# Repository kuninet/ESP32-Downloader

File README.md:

# ESP32/ESP8266 Downloader基板

## 概要
* ESP32/ESP8266 Downloader基板です。
* ピン配置は ESP32 Downloader kitに合わせています。
* MOS FET x2個で自動書き込み回路を装備してしています。
* USBシリアルICはCH340Kを使用しています。

## 回路図
[回路図](image/ESP32-Downloder.pdf)

## イメージ

## 参考
* ESP32 Downloader kit
  * https://docs.m5stack.com/ja/accessory/esp32_downloader_kit

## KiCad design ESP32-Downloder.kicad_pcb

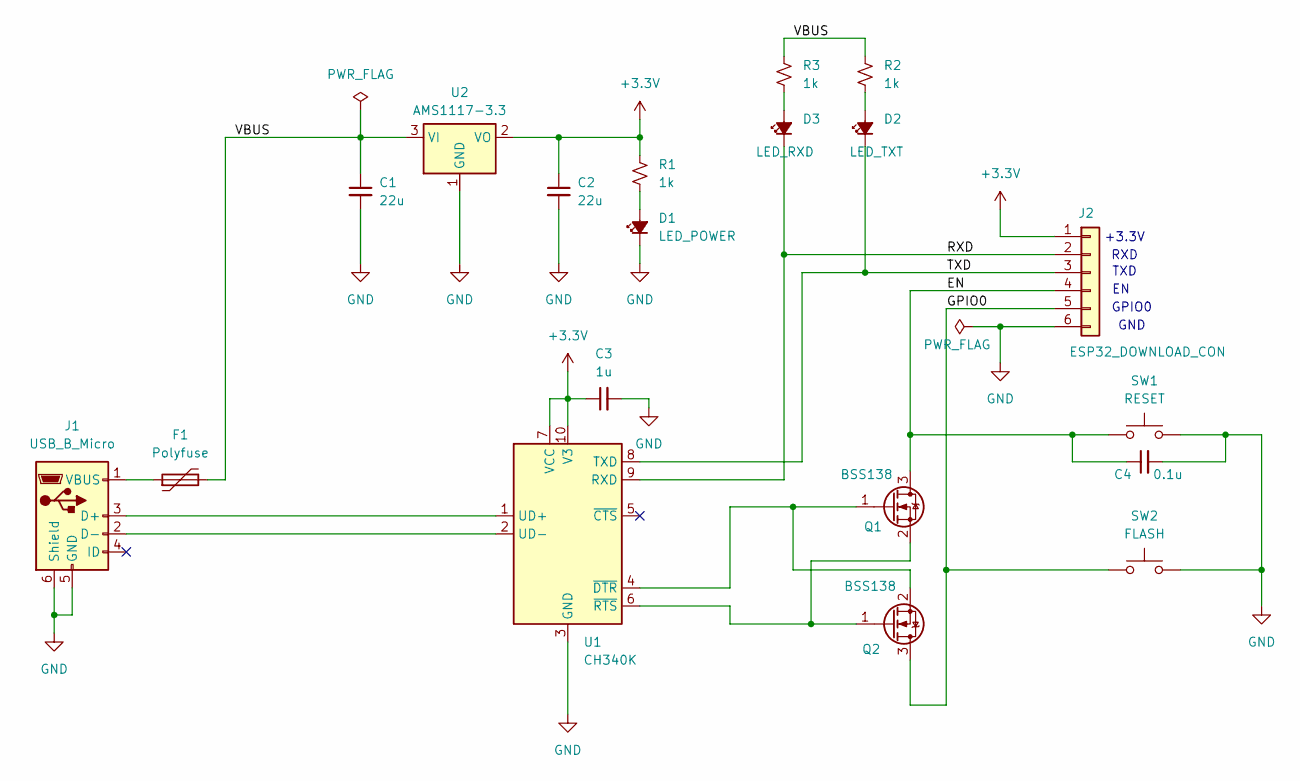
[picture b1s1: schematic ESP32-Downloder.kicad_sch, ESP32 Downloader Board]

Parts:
C1, C2: 22u; C_0603_1608Metric_Pad1.08x0.95mm_HandSolder
C3: 1u; C_0603_1608Metric_Pad1.08x0.95mm_HandSolder
C4: 0.1u; C_0603_1608Metric_Pad1.08x0.95mm_HandSolder
D1: LED_POWER; LED_0603_1608Metric_Pad1.05x0.95mm_HandSolder
D2: LED_TXT; LED_0603_1608Metric_Pad1.05x0.95mm_HandSolder
D3: LED_RXD; LED_0603_1608Metric_Pad1.05x0.95mm_HandSolder
F1: Polyfuse; Fuse_1206_3216Metric_Pad1.42x1.75mm_HandSolder
J1: USB_B_Micro; USB_Micro-B_Molex-105017-0001
J2: ESP32_DOWNLOAD_CON; PinSocket_1x06_P2.54mm_Horizontal
Q1, Q2: BSS138; SOT-23
R1, R2, R3: 1k; R_0603_1608Metric_Pad0.98x0.95mm_HandSolder
SW1: RESET; SW_Push_SPST_NO_Alps_SKRK
SW2: FLASH; SW_Push_SPST_NO_Alps_SKRK
U1: CH340K; SSOP-10-1EP_3.9x4.9mm_P1mm_EP2.1x3.3mm
U2: AMS1117-3.3; SOT-223-3_TabPin2

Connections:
+3.3V: C2.1, C3.1, J2.1, R1.1, U1.7 (VCC), U1.10 (V3), U2.2 (VO)
/EN: C4.1, J2.4, Q1.3 (D), SW1.1
/GPIO0: J2.5, Q2.3 (D), SW2.1
/RXD: D3.1 (K), J2.2, U1.9 (RXD)
/TXD: D2.1 (K), J2.3, U1.8 (TXD)
/VBUS: C1.1, F1.2, R2.1, R3.1, U2.3 (VI)
GND: C1.2, C2.2, C3.2, C4.2, D1.1 (K), J1.5 (GND), J1.6 (Shield), J2.6, SW1.2, SW2.2, U1.3 (GND), U1.11 (GND), U2.1 (GND)
unnamed: D1.2 (A), R1.2
unnamed: D2.2 (A), R2.2
unnamed: D3.2 (A), R3.2
unnamed: J1.3 (D+), U1.1 (UD+)
unnamed: J1.2 (D-), U1.2 (UD-)
unnamed: F1.1, J1.1 (VBUS)
unnamed: Q1.1 (G), Q2.2 (S), U1.4 (~DTR)
unnamed: Q1.2 (S), Q2.1 (G), U1.6 (~RTS)

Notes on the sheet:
GND
TXD
+3.3V
GPIO0
RXD

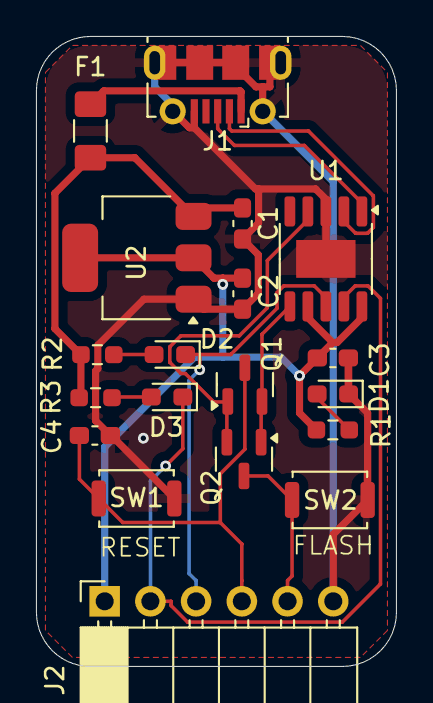
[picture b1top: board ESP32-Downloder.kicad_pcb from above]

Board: 2 copper layers, 20.0 x 35.0 mm, 19 parts (0 on the bottom side), 15 nets.

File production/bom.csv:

Designator,Footprint,Quantity,Value,LCSC Part #
"C1, C2",0603,2,22u,
C3,0603,1,1u,
C4,0603,1,0.1u,
D1,0603,1,LED_POWER,
D2,0603,1,LED_TXT,
D3,0603,1,LED_RXD,
F1,1206,1,Polyfuse,
J1,USB_Micro-B_Molex-105017-0001,1,USB_B_Micro,
J2,PinSocket_1x06_P2.54mm_Horizontal,1,ESP32_DOWNLOAD_CON,
"Q1, Q2",SOT-23,2,BSS138,
"R1, R2, R3",0603,3,1k,
SW1,SW_Push_SPST_NO_Alps_SKRK,1,RESET,
SW2,SW_Push_SPST_NO_Alps_SKRK,1,FLASH,
U1,SSOP-10-1EP_3.9x4.9mm_P1mm_EP2.1x3.3mm,1,CH340K,
U2,SOT-223-3_TabPin2,1,AMS1117-3.3,

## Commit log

2025-05-19 init
2025-06-01 README追加、ガーバーデータ出力
2025-06-01 Create LICENSE
2025-06-01 3Dイメージ追加
